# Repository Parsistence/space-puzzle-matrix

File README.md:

# Space Puzzle Matrix

A puzzle matrix module designed for a space panel to be used by the Christa McAuliffe Space Center.

## Overview

The matrix module will be a matrix of 6x6 LED buttons that will allow different puzzles to be played. The matrix will also have a small LCD display and 3 additional buttons for added functionality. The games will be played on the button matrix and encourage problem-solving and critical thinking skills.

## Games

The games will be programmed with scalable difficulty. A few games that will be implemented:

- **Puzzle Panel**: Tap one tile to flip the surrounding tiles. You have a limited number of flips to match the reference matrix, and the number of flips increases with difficulty. Based on [this game from New Super Mario Bros DS](https://www.youtube.com/watch?v=6mqAMbGBhQw&t=5s).
- **Simon Says**: One button will light up, then the player must push that button. Then, a sequence of two buttons will light up on after the other, and the player must push those buttons in the order they appeared. This is essentially just a normal game of simon says, played on a larger matrix.
- **Minesweeper**: Several mines will be placed on the matrix that the player cannot see. When a player taps on a tile, it lights up, and its color indicates the number of mines adjacent to it.
- **Flow**: Connect several pipes to allow water to flow from them. Each pipe has two endpoints on the matrix, and the player connects the endpoints by pushing adjacent buttons to create a path.
- **Maze**: A maze randomly generates on the matrix, and the player has to draw a path from the start to the finish to succeed. In higher difficulties the player's path must be the shortest possible path in order to succeed.
- **Navigation**: The player must guide a robot to a few target spaces in a maze. The player must provide the robot with a set of instructions (move forward, rotate left, rotate right) in order to map the robot's route. Based on [The Navigator](https://clubpenguin.fandom.com/wiki/The_Navigator) from Club Penguin.

More detail on each game and how they will be implemented will be added to [**Games & Implementation**](./Games%20&%20Implementation.md).

## Hardware

The matrix module will use a 6x6 matrix of LED buttons, along with an LCD display and a few additional buttons on the side. A more comprehensive list of parts will be added to [**Part List**](./Part%20List.md).

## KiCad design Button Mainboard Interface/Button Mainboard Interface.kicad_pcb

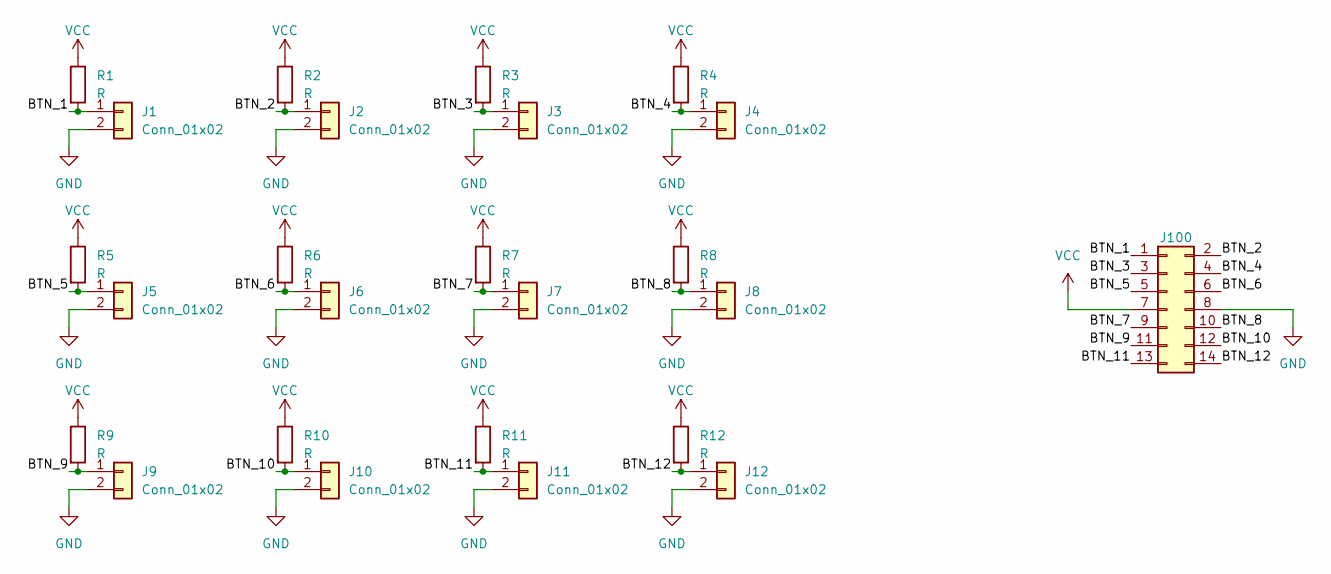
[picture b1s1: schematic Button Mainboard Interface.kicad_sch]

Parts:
J1, J2, J3, J4, J5, J6, J7, J8, J9, J10, J11, J12: Conn_01x02; JST_XH_B2B-XH-A_1x02_P2.50mm_Vertical
J100: Conn_02x07_Odd_Even; IDC-Header_2x07_P2.54mm_Vertical
R1, R2, R3, R4, R5, R6, R7, R8, R9, R10, R11, R12: R; R_0805_2012Metric_Pad1.20x1.40mm_HandSolder

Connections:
/BTN_1: J1.1, J100.1, R1.2
/BTN_2: J2.1, J100.2, R2.2
/BTN_3: J3.1, J100.3, R3.2
/BTN_4: J4.1, J100.4, R4.2
/BTN_5: J5.1, J100.5, R5.2
/BTN_6: J6.1, J100.6, R6.2
/BTN_7: J7.1, J100.9, R7.2
/BTN_8: J8.1, J100.10, R8.2
/BTN_9: J9.1, J100.11, R9.2
/BTN_10: J10.1, J100.12, R10.2
/BTN_11: J11.1, J100.13, R11.2
/BTN_12: J12.1, J100.14, R12.2
GND: J1.2, J2.2, J3.2, J4.2, J5.2, J6.2, J7.2, J8.2, J9.2, J10.2, J11.2, J12.2, J100.8
VCC: J100.7, R1.1, R2.1, R3.1, R4.1, R5.1, R6.1, R7.1, R8.1, R9.1, R10.1, R11.1, R12.1

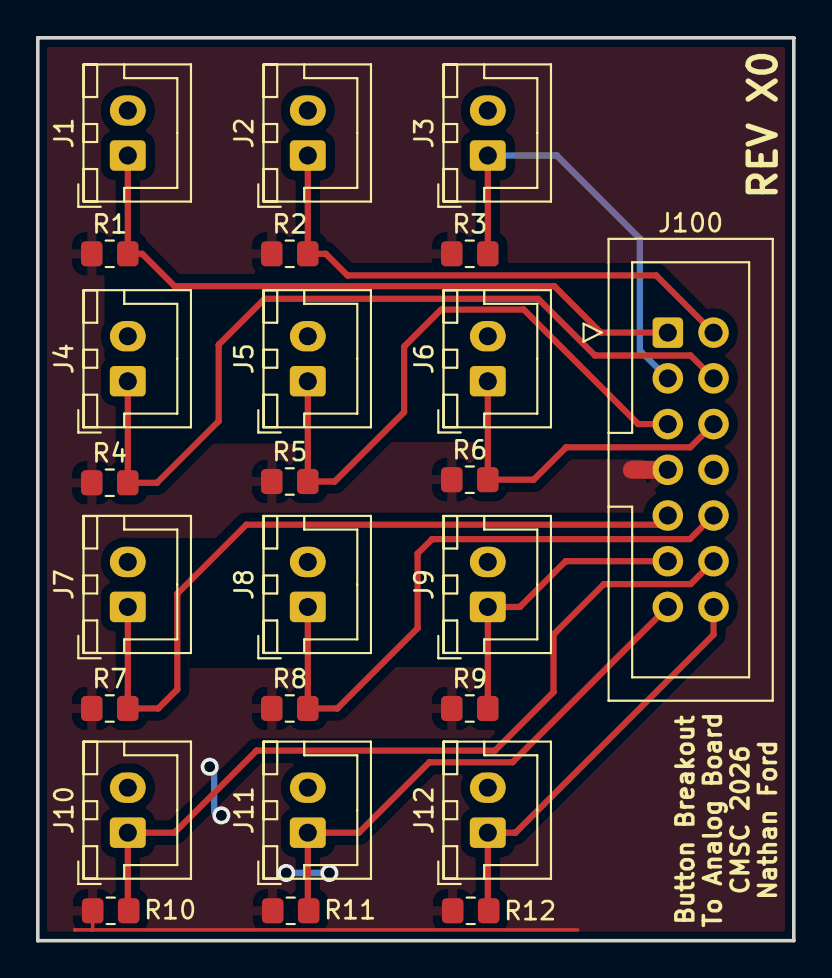
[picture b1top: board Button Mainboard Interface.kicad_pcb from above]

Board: 2 copper layers, 42.0 x 50.2 mm, 25 parts (0 on the bottom side), 14 nets.

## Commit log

2025-10-10 Initial readme commit
2025-10-10 Create Part List.md
    Ideas for what parts we'll need
2025-10-10 Add sketch image to readme and list games we plan to implement
2025-10-10 Reference Part List in main README
2025-10-10 Worked on the definition a little bit more
2025-10-10 Add new navigation game idea to README
2025-10-10 Remove stub sections from README
2025-10-10 Add .gitignore for .vscode/ directory
2025-10-10 Add info on additional readmes to README.md
2025-10-10 expand NSMBDS acronym for clarity
2025-10-10 Expanded definitions
2025-10-10 Update README title and image caption
2025-10-10 Fix Puzzle Panel link in README
2025-10-17 Fixed spacing in Devlog.md
2025-10-17 Added Devlog.md to track development process. Added a short entry for today's progress.
2025-10-17 Added block diagram to readme
2025-10-17 Add block diagram to devlog
2025-10-17 Revise formatting for Part List.md
2025-10-17 Create stub parts list
2025-10-17 Rename Part List Ideas to Part List
2025-10-24 update part list
2025-10-24 add neopixel to part list
2025-10-24 Update neopixel in part list
2025-10-24 Update part list with links and costs
2025-11-07 Switched to Arcade
    Updated part list with new button links and costs.
2025-11-07 Changed spacing for Arcade buttons
2025-11-07 Basic terminal game implementation
2025-11-14 Updated simon says game
2025-11-14 Create empty neopixels.ino for experimenting with neopixels
2025-11-14 update devlog
2025-11-20 update example neopixel code
2025-11-20 Update devlog for 11/19
2026-01-09 add new arduino sketch that toggles light with a push button
2026-01-16 Refactor and improve neopixel_button.ino
2026-01-16 relocate examples/neopixel_button/matrix.h into its own arduino sketch
2026-01-16 update neopixel_matrix.ino with example code from the NeoMatrix repository
2026-01-16 Created PCB for Buttons
2026-01-16 Released PCB
2026-01-16 Upodate neopixel_matrix.ino to change colors on grid
